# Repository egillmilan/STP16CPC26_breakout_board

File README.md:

# STP16CPC26_breakout_board
A breakout board for easy prototyping with the STP16CPC26 constant current LED driver. The two pin rows are spaced 0.7" apart, making them compatible with breadboards.

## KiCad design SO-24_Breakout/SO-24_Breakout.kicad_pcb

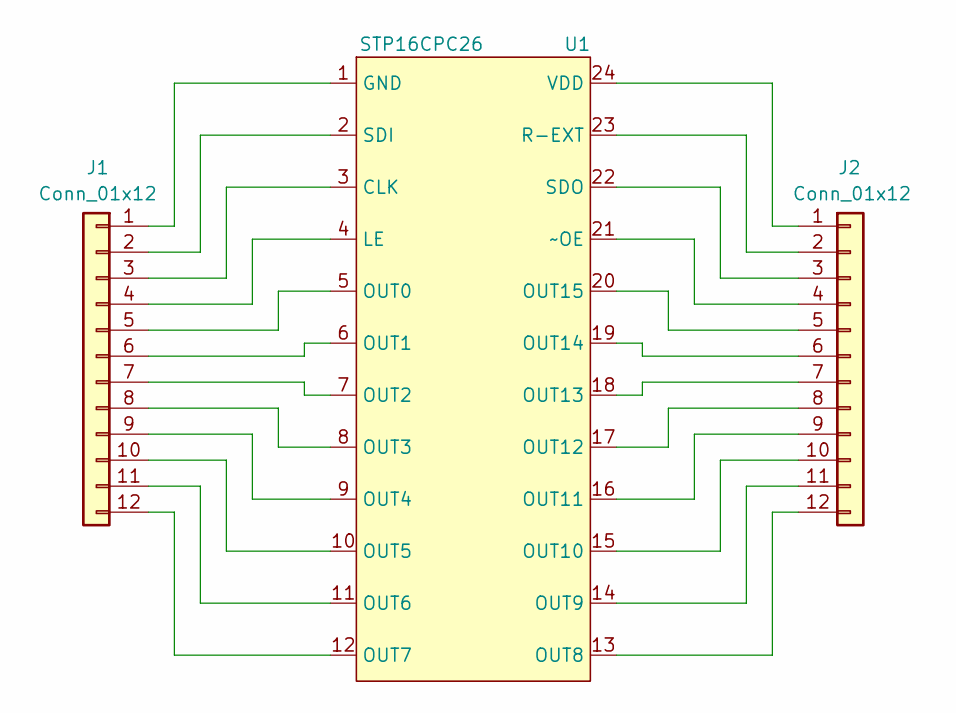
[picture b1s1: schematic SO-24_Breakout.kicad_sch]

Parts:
J1: Conn_01x12; PinHeader_1x12_P2.54mm_Vertical
J2: Conn_01x12; PinHeader_1x12_P2.54mm_Vertical_No_GND
U1: STP16CPC26; SOIC-24W_7.5x15.4mm_P1.27mm

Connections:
unnamed: J1.1, U1.1 (GND)
unnamed: J1.2, U1.2 (SDI)
unnamed: J1.3, U1.3 (CLK)
unnamed: J1.4, U1.4 (LE)
unnamed: J1.5, U1.5 (OUT0)
unnamed: J1.6, U1.6 (OUT1)
unnamed: J1.7, U1.7 (OUT2)
unnamed: J1.8, U1.8 (OUT3)
unnamed: J1.9, U1.9 (OUT4)
unnamed: J1.10, U1.10 (OUT5)
unnamed: J1.11, U1.11 (OUT6)
unnamed: J1.12, U1.12 (OUT7)
unnamed: J2.1, U1.24 (VDD)
unnamed: J2.2, U1.23 (R-EXT)
unnamed: J2.3, U1.22 (SDO)
unnamed: J2.4, U1.21 (~OE)
unnamed: J2.5, U1.20 (OUT15)
unnamed: J2.6, U1.19 (OUT14)
unnamed: J2.7, U1.18 (OUT13)
unnamed: J2.8, U1.17 (OUT12)
unnamed: J2.9, U1.16 (OUT11)
unnamed: J2.10, U1.15 (OUT10)
unnamed: J2.11, U1.14 (OUT9)
unnamed: J2.12, U1.13 (OUT8)

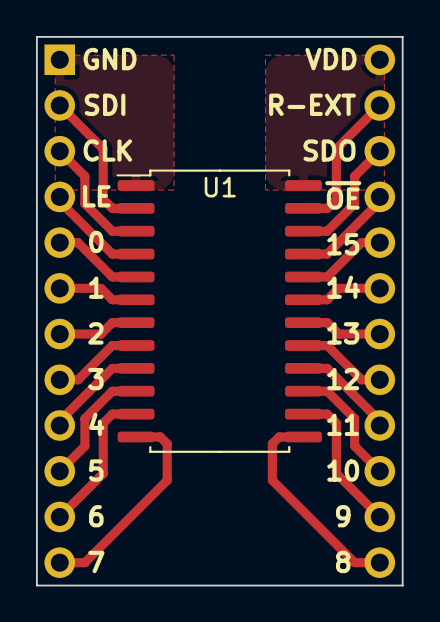
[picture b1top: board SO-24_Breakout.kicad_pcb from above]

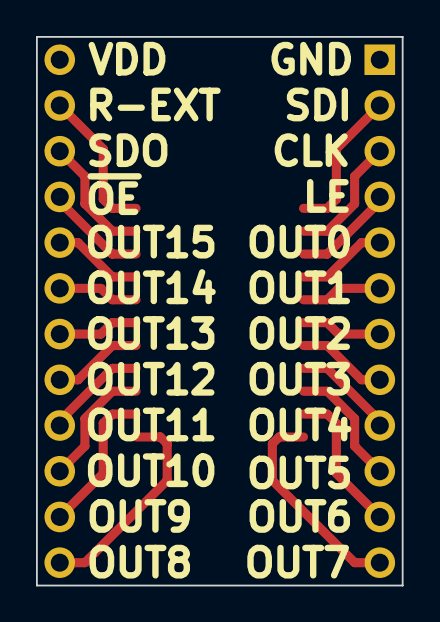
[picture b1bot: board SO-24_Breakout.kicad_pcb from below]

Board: 2 copper layers, 20.3 x 30.5 mm, 3 parts (2 on the bottom side), 24 nets.
